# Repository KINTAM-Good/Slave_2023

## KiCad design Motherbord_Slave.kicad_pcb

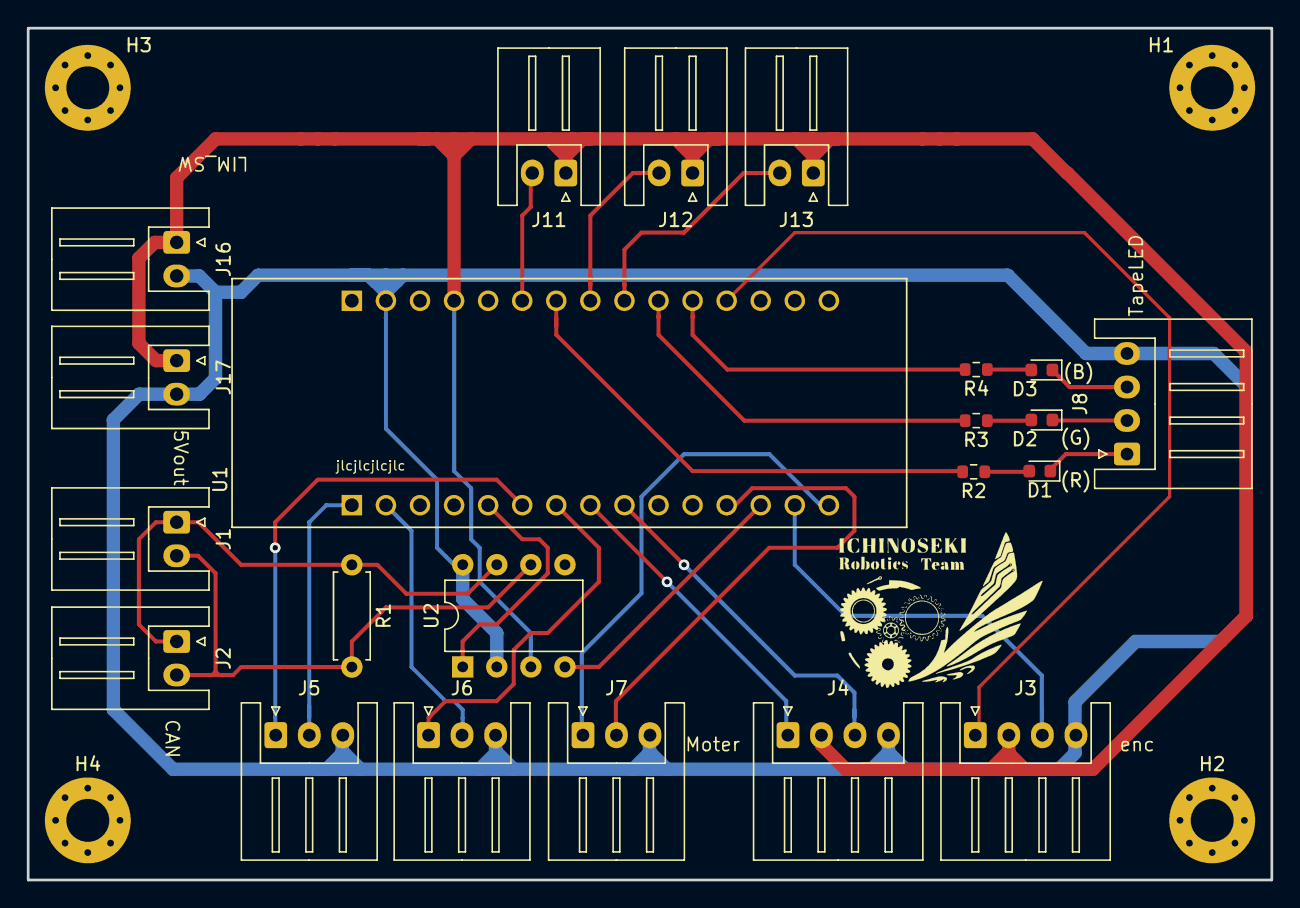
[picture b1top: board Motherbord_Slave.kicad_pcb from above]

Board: 2 copper layers, 92.7 x 63.5 mm, 27 parts (0 on the bottom side), 28 nets.

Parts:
D1, D2, D3: LED; LED_0603_1608Metric
H1, H2, H3, H4: MountingHole; MountingHole_3.2mm_M3_Pad_Via
J1, J2, J11, J12, J13, J16, J17: Conn_01x02_Pin; JST_XH_S2B-XH-A_1x02_P2.50mm_Horizontal
J3, J4, J8#2: Conn_01x04_Pin; JST_XH_S4B-XH-A_1x04_P2.50mm_Horizontal
J5, J6, J7: Conn_01x03_Pin; JST_XH_S3B-XH-A_1x03_P2.50mm_Horizontal
J8: Logo; INCT
R1: R; R_Axial_DIN0207_L6.3mm_D2.5mm_P7.62mm_Horizontal
R2, R3, R4: R; R_0603_1608Metric
U1: mbed_Nucleo-L432KC; MODULE_NUCLEO-L432KC
U2: MCP2561-E-P; DIP-8_W7.62mm

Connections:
+5V: J3.2, J4.2, J11.1, J12.1, J13.1, J16.1, J17.1, U1.27 (5V), U2.3 (VDD)
CAN_rd: U1.13 (D10), U2.4 (RXD)
CAN_td: U1.5 (D2), U2.1 (TXD)
Dir_1: J5.1, U1.6 (D3)
Dir_2: J6.1, U1.7 (D4)
Dir_3: J7.1, U1.15 (D12)
GND: J3.4, J4.4, J5.3, J6.3, J7.3, J8#2.4, J16.2, J17.2, U1.29 (GND), U2.2 (VSS), U2.8 (STBY)
LED_B: R4.2, U1.20 (A1)
LED_G: R3.2, U1.21 (A2)
LED_R: R2.2, U1.24 (A5)
LIM_SW3: J11.2, U1.25 (A6)
LIM_SW4: J12.2, U1.23 (A4)
LIM_SW5: J13.2, U1.22 (A3)
unnamed: D1.2 (A), R2.1
unnamed: D1.1 (K), J8#2.1
unnamed: D2.2 (A), R3.1
unnamed: D2.1 (K), J8#2.2
unnamed: D3.2 (A), R4.1
unnamed: D3.1 (K), J8#2.3
unnamed: J1.1, J2.1, R1.1, U2.7 (CANH)
unnamed: J1.2, J2.2, R1.2, U2.6 (CANL)
PWM_1: J5.2, U1.1 (D1/TX)
PWM_2: J6.2, U1.2 (D0/RX)
PWM_3: J7.2, U1.12 (D9)
enc_1_a: J4.1, U1.8 (D5)
enc_1_b: J4.3, U1.9 (D6)
enc_2_a: J3.1, U1.19 (A0)
enc_2_b: J3.3, U1.14 (D11)
